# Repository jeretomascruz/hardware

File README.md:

# Hardware Monorepo (KiCad)

Este repositorio agrupa múltiples proyectos de hardware.

## Proyectos
- sensado-soldadoras/: Módulo de sensado (KiCad), con kicad/, outputs/, mechanical/, docs/.

## Flujos
- Versionar releases por proyecto usando tags por convención, por ejemplo: sensado-soldadoras-hw-v1.0 o hw-v1.0 si el repo contiene un único proyecto activo.
- Subir Gerbers/BOM/PickPlace y PDFs a cada Release.
- Usar Git LFS (configurado en .gitattributes) para binarios.

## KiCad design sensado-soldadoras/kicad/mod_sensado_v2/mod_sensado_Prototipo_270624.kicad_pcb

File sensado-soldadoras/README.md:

# Sensado Soldadoras - Hardware (KiCad)

Repositorio de diseños de hardware (KiCad) para el sistema de sensado.

## Estructura
- kicad/: archivos fuente del proyecto KiCad (.kicad_pro, .kicad_sch, .kicad_pcb, librerías)
- outputs/: archivos de fabricación
  - gerbers/, om/, pickplace/, pdf/
- mechanical/: modelos 3D y mecánica (STEP, STL, etc.)
- docs/: documentación, datasheets, fotos

## Buenas prácticas
- Versionado de HW por tags: hw-v1.0, hw-v1.1.
- Adjuntar Gerbers, BOM y Pick&Place en cada Release.
- Usar Git LFS para binarios pesados (STEP/PDF/ZIP).

## Generar outputs
- Exporta Gerbers, BOM (CSV) y Pick&Place desde KiCad y colócalos en outputs/.
- Exporta esquemáticos y PCB a PDF a outputs/pdf/.

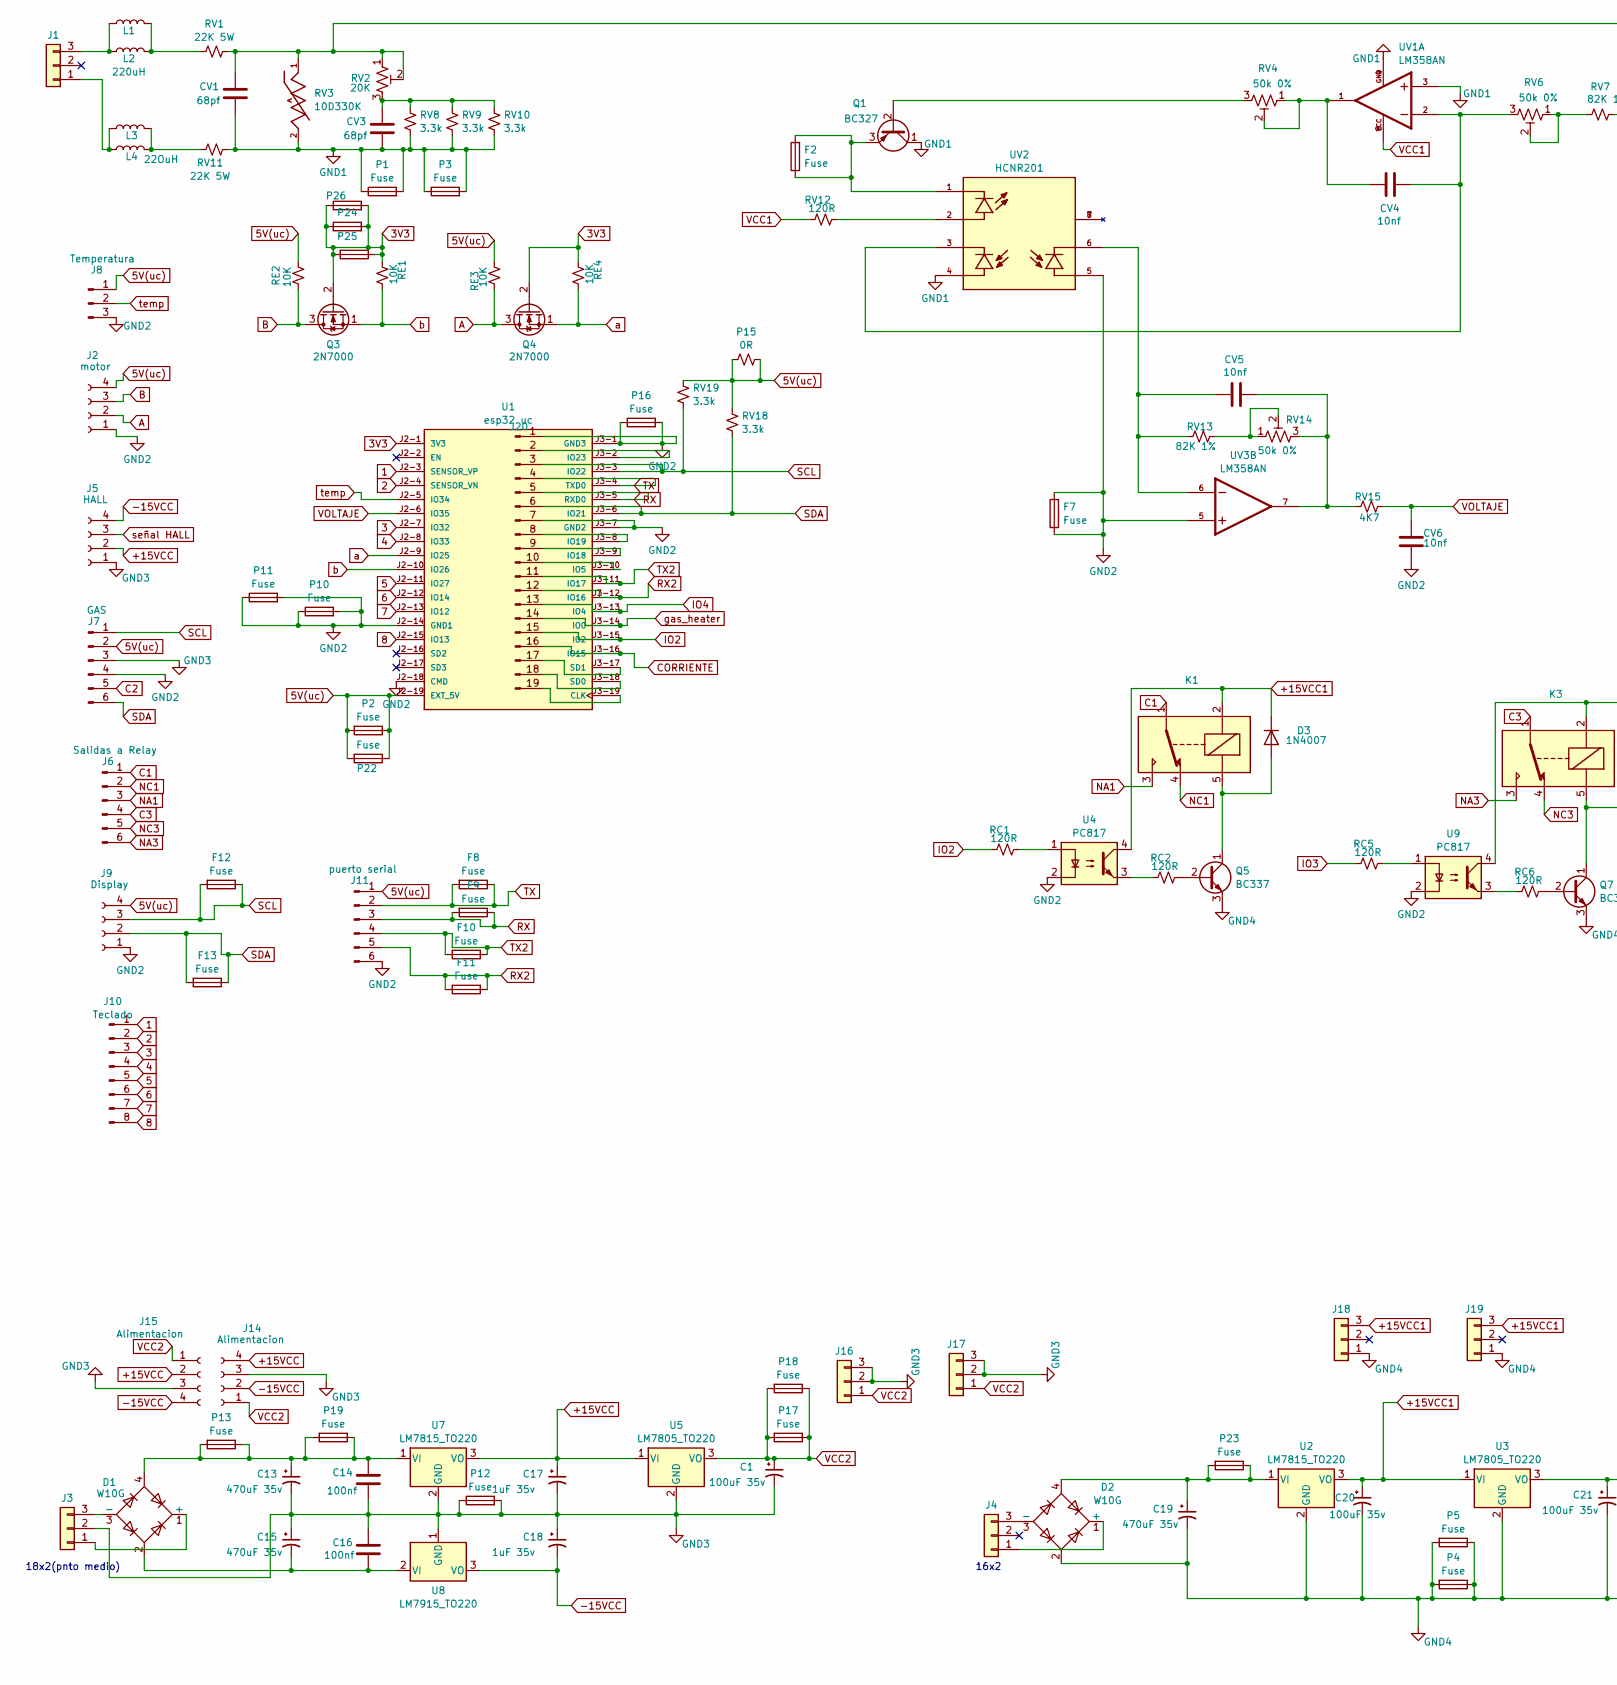
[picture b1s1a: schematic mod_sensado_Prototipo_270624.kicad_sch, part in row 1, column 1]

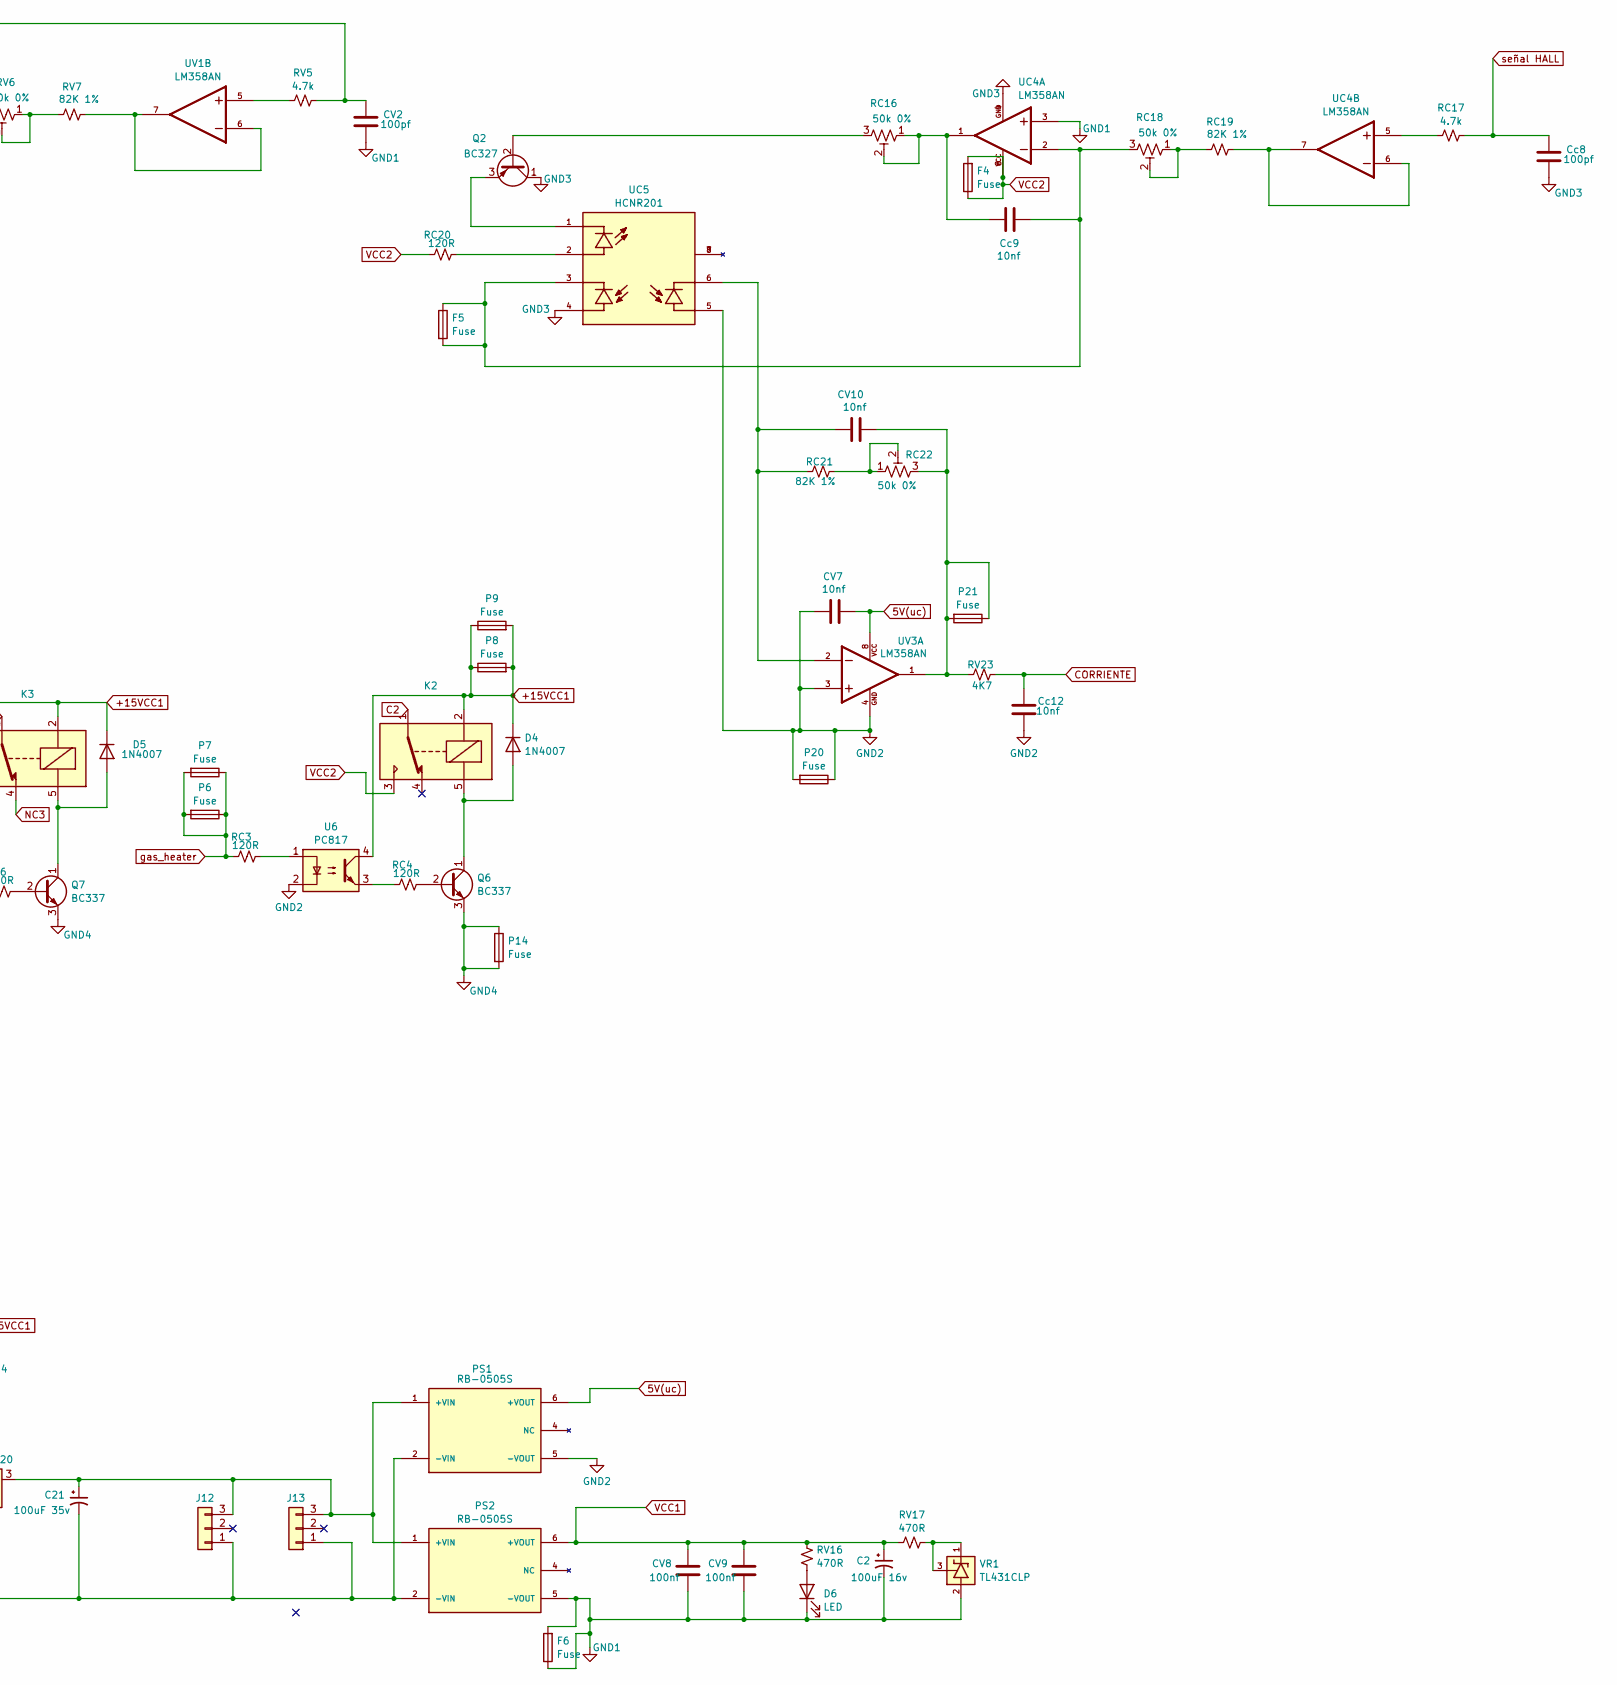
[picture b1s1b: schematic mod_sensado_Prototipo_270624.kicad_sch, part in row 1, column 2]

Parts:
C1, C20, C21: 100uF 35v; CP_Radial_D8.0mm_P2.50mm
C2: 100uF 16v; CP_Radial_D8.0mm_P2.50mm
C13, C15, C19: 470uF 35v; CP_Radial_D8.0mm_P2.50mm
C14, C16: 100nf; C_Disc_D4.7mm_W2.5mm_P5.00mm
C17, C18: 1uF 35v; CP_Radial_D8.0mm_P2.50mm
CV1, CV3: 68pf; C_Disc_D4.7mm_W2.5mm_P5.00mm
CV2: 100pf; C_Disc_D4.7mm_W2.5mm_P5.00mm
CV4, CV5, CV6, CV7, CV10: 10nf; C_Disc_D4.7mm_W2.5mm_P5.00mm
CV8, CV9: 100nf; C_Disc_D4.7mm_W2.5mm_P5.00mm
Cc8: 100pf; C_Disc_D4.7mm_W2.5mm_P5.00mm
Cc9, Cc12: 10nf; C_Disc_D4.7mm_W2.5mm_P5.00mm
D1, D2: W10G; Diode_Bridge_Round_D9.8mm
D3, D4, D5: 1N4007; D_DO-41_SOD81_P10.16mm_Horizontal
D6: LED; LED_D3.0mm_Clear
F2, F4, F5, F6, F7, F8, F9, F10, F11, F12, F13: Fuse; R_Axial_DIN0207_L6.3mm_D2.5mm_P7.62mm_Horizontal
J1, J3, J4, J12, J13, J16, J17, J18, J19: Conn_01x03; Molex_KK-396_5273-03A_1x03_P3.96mm_Vertical
J2: motor; Altech_AK100_1x04_P5.00mm
J5: HALL; Altech_AK100_1x04_P5.00mm
J6: Salidas a Relay; JST_VH_B6P-VH_1x06_P3.96mm_Vertical
J7: GAS; TerminalBlock_MetzConnect_Type205_RT04506UBLC_1x06_P5.00mm_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
J8: Temperatura; Altech_AK100_1x03_P5.00mm
J9: Display; Altech_AK100_1x04_P5.00mm
J10: Teclado; PinHeader_1x10_P2.54mm_Vertical
J11: puerto serial; TerminalBlock_MetzConnect_Type205_RT04506UBLC_1x06_P5.00mm_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
J14, J15: Alimentacion; Molex_KK-396_A-41791-0004_1x04_P3.96mm_Vertical
J20: Conn_01x19_Pin; PinHeader_1x19_P2.54mm_Vertical
K1, K2, K3: SANYOU_SRD_Form_C; Relay_SPDT_SANYOU_SRD_Series_Form_C
L1: 220uH; L_Neosid_SM-PIC0512H
L2: 220uH; L_Axial_L9.5mm_D4.0mm_P12.70mm_Horizontal_Fastron_SMCC
L3: 22OuH; L_Neosid_SM-PIC0512H
L4: 22OuH; L_Axial_L9.5mm_D4.0mm_P12.70mm_Horizontal_Fastron_SMCC
P1, P2, P3, P4, P5, P6, P7, P8, P9, P10, P11, P12, P13, P14, P16, P17, P18, P19, P20, P21, P22, P23, P24, P25, P26: Fuse; R_Axial_DIN0207_L6.3mm_D2.5mm_P7.62mm_Horizontal
P15: 0R; R_Axial_DIN0309_L9.0mm_D3.2mm_P15.24mm_Horizontal
PS1, PS2: RB-0505S; RB-0505S convertidor; PARTREV 0/2015
Q1, Q2: BC327; TO-92_Wide
Q3, Q4: 2N7000; TO-92_Wide
Q5, Q6, Q7: BC337; TO-92_Wide
RC1, RC2, RC3, RC4, RC5, RC6, RC20: 120R; R_Axial_DIN0309_L9.0mm_D3.2mm_P15.24mm_Horizontal
RC16, RC18, RC22: 50k 0%; Potentiometer_Runtron_RM-063_Horizontal
RC17: 4.7k; R_Axial_DIN0309_L9.0mm_D3.2mm_P15.24mm_Horizontal
RC19, RC21: 82K 1%; R_Axial_DIN0309_L9.0mm_D3.2mm_P15.24mm_Horizontal
RE1, RE2, RE3, RE4: 10K; R_Axial_DIN0309_L9.0mm_D3.2mm_P15.24mm_Horizontal
RV1, RV11: 22K 5W; R_Axial_Power_L25.0mm_W9.0mm_P30.48mm
RV2: 20K; Potentiometer_Runtron_RM-063_Horizontal
RV3: 10D330K; Varistor; PARTREV Jan-18
RV4, RV6, RV14: 50k 0%; Potentiometer_Runtron_RM-063_Horizontal
RV5: 4.7k; R_Axial_DIN0309_L9.0mm_D3.2mm_P15.24mm_Horizontal
RV7, RV13: 82K 1%; R_Axial_DIN0309_L9.0mm_D3.2mm_P15.24mm_Horizontal
RV8, RV9, RV10, RV18, RV19: 3.3k; R_Axial_DIN0309_L9.0mm_D3.2mm_P15.24mm_Horizontal
RV12: 120R; R_Axial_DIN0309_L9.0mm_D3.2mm_P15.24mm_Horizontal
RV15, RV23: 4K7; R_Axial_DIN0309_L9.0mm_D3.2mm_P15.24mm_Horizontal
RV16, RV17: 470R; R_Axial_DIN0309_L9.0mm_D3.2mm_P15.24mm_Horizontal
U1: esp32 uc; ESP32-module; PARTREV V4
U2, U7: LM7815_TO220; TO-220-3_Vertical
U3, U5: LM7805_TO220; TO-220-3_Vertical
U4, U6, U9: PC817; DIP-4_W7.62mm
U8: LM7915_TO220; TO-220-3_Vertical
UC4: LM358AN; lm358
UC5: HCNR201; hcn201; PARTREV July 1, 2014
UV1, UV3: LM358AN; lm358
UV2: HCNR201; hcn201; PARTREV July 1, 2014
VR1: TL431CLP; TO-92; PARTREV R

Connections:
1: J10.1, U1.J2-3 (SENSOR_VP)
2: J10.2, U1.J2-4 (SENSOR_VN)
3: J10.3, U1.J2-7 (IO32)
3V3: P24.1, P24.2, P25.1, P25.2, P26.1, P26.2, Q3.2 (G), Q4.2 (G), RE1.2, RE4.2, U1.J2-1 (3V3)
4: J10.4, U1.J2-8 (IO33)
5: J10.5, U1.J2-11 (IO27)
5V(uc): CV7.2, J2.4, J7.2, J8.1, J9.4, J11.1, P2.1, P2.2, P15.1, P15.2, P22.1, P22.2, PS1.6 (+VOUT), RE2.1, RE3.1, RV18.2, RV19.2, U1.J2-19 (EXT_5V), UV3.8
6: J10.6, U1.J2-12 (IO14)
7: J10.7, U1.J2-13 (IO12)
8: J10.8, U1.J2-15 (IO13)
+15VCC: C17.1, J5.2, J14.4, J15.2, U5.1 (VI), U7.3 (VO)
+15VCC1: C20.1, D3.1 (K), D4.1 (K), D5.1 (K), J18.3, J19.3, K1.2, K2.2, K3.2, P8.1, P8.2, P9.1, P9.2, U2.3 (VO), U3.1 (VI), U4.4, U6.4, U9.4
-15VCC: C18.2, J5.4, J14.2, J15.4, U8.3 (VO)
A: J2.2, Q4.3 (D), RE3.2
B: J2.3, Q3.3 (D), RE2.2
C1: J6.1, K1.1
C2: J7.5, K2.1
C3: J6.4, K3.1
CORRIENTE: Cc12.2, J20.16, RV23.2, U1.J3-16 (IO15)
GND1: C2.2, CV1.2, CV2.2, CV3.2, CV8.2, CV9.2, D6.1 (K), F6.1, F6.2, P1.1, P1.2, P3.1, P3.2, PS2.5 (-VOUT), Q1.1 (C), RV3.2, RV8.1, RV9.1, RV10.1, RV11.2, UC4.3, UV1.3, UV1.4, UV2.4, VR1.2
GND2: CV6.1, CV7.1, Cc12.1, F7.1, F7.2, J2.1, J7.4, J8.3, J9.1, J11.6, J20.1, J20.7, P10.1, P10.2, P11.1, P11.2, P16.1, P16.2, P20.1, P20.2, PS1.5 (-VOUT), U1.J2-14 (GND1), U1.J2-18 (CMD), U1.J3-1 (GND3), U1.J3-7 (GND2), U4.2, U6.2, U9.2, UC5.5, UV2.5, UV3.3, UV3.4, UV3.5
GND3: C1.2, C13.2, C14.2, C15.1, C16.1, C17.2, C18.1, Cc8.2, J3.2, J5.1, J7.3, J14.3, J15.3, J16.2, J16.3, J17.2, J17.3, P12.1, P12.2, Q2.1 (C), U5.2 (GND), U7.2 (GND), U8.1 (GND), UC4.4, UC5.4
GND4: C19.2, C20.2, C21.2, D2.2, J12.1, J13.1, J18.1, J19.1, P4.1, P4.2, P5.1, P5.2, P14.1, P14.2, PS1.2 (-VIN), PS2.2 (-VIN), Q5.3 (E), Q6.3 (E), Q7.3 (E), U2.2 (GND), U3.2 (GND)
IO2: J20.15, RC1.2, U1.J3-15 (IO2)
IO3: RC5.2
IO4: J20.13, U1.J3-13 (IO4)
NA1: J6.3, K1.3
NA3: J6.6, K3.3
NC1: J6.2, K1.4
NC3: J6.5, K3.4
unnamed: CV1.1, CV2.1, RV1.2, RV2.1, RV2.2, RV3.1, RV5.1
unnamed: CV3.1, RV2.3, RV8.2, RV9.2, RV10.2
unnamed: CV4.1, RV4.1, RV4.2, UV1.1
unnamed: CV4.2, RV6.3, UV1.2, UV2.3
unnamed: CV5.1, RV13.1, UV2.6, UV3.6
unnamed: CV5.2, RV14.3, RV15.1, UV3.7
unnamed: CV10.1, RC21.1, UC5.6, UV3.2
unnamed: CV10.2, P21.1, P21.2, RC22.3, RV23.1, UV3.1
unnamed: Cc9.1, RC16.1, RC16.2, UC4.1
unnamed: Cc9.2, F5.1, F5.2, RC18.3, UC4.2, UC5.3
unnamed: D1.1 (+), J3.1
unnamed: D1.3 (-), J3.3
unnamed: D2.1 (+), J4.1
unnamed: D2.3 (-), J4.3
unnamed: D3.2 (A), K1.5, Q5.1 (C)
unnamed: D4.2 (A), K2.5, Q6.1 (C)
unnamed: D5.2 (A), K3.5, Q7.1 (C)
unnamed: D6.2 (A), RV16.1
unnamed: J1.1, L3.1, L4.1
unnamed: J1.3, L1.1, L2.1
unnamed: C21.1, J12.3, J13.3, PS1.1 (+VIN), PS2.1 (+VIN), U3.3 (VO)
unnamed: J20.2, U1.J3-2 (IO23)
unnamed: J20.8, U1.J3-8 (IO19)
unnamed: J20.9, U1.J3-9 (IO18)
unnamed: J20.10, U1.J3-10 (IO5)
unnamed: J20.17, U1.J3-17 (SD1)
unnamed: J20.18, U1.J3-18 (SD0)
unnamed: J20.19, U1.J3-19 (CLK)
unnamed: L1.2, L2.2, RV1.1
unnamed: L3.2, L4.2, RV11.1
unnamed: Q1.2 (B), RV4.3
unnamed: F2.1, F2.2, Q1.3 (E), UV2.1
unnamed: Q2.2 (B), RC16.3
unnamed: Q2.3 (E), UC5.1
unnamed: Q5.2 (B), RC2.1
unnamed: Q6.2 (B), RC4.1
unnamed: Q7.2 (B), RC6.1
unnamed: RC1.1, U4.1
unnamed: RC2.2, U4.3
unnamed: RC3.1, U6.1
unnamed: RC4.2, U6.3
unnamed: RC5.1, U9.1
unnamed: RC6.2, U9.3
unnamed: RC17.2, UC4.5
unnamed: RC18.1, RC18.2, RC19.2
unnamed: RC19.1, UC4.6, UC4.7
unnamed: RC20.1, UC5.2
unnamed: RC21.2, RC22.1, RC22.2
unnamed: RV5.2, UV1.5
unnamed: RV6.1, RV6.2, RV7.2
unnamed: RV7.1, UV1.6, UV1.7
unnamed: RV12.1, UV2.2
unnamed: RV13.2, RV14.1, RV14.2
unnamed: RV17.1, VR1.1, VR1.3
unnamed: C19.1, D2.4, P23.1, P23.2, U2.1 (VI)
unnamed: C13.1, C14.1, D1.4, P13.1, P13.2, P19.1, P19.2, U7.1 (VI)
unnamed: C15.2, C16.2, D1.2, U8.2 (VI)
RX: F9.1, F9.2, J11.3, J20.5, U1.J3-5 (RXD0)
RX2: F11.1, F11.2, J11.5, J20.12, U1.J3-12 (IO16)
SCL: F12.1, F12.2, J7.1, J9.3, J20.3, RV19.1, U1.J3-3 (IO22)
SDA: F13.1, F13.2, J7.6, J9.2, J20.6, RV18.1, U1.J3-6 (IO21)
TX: F8.1, F8.2, J11.2, J20.4, U1.J3-4 (TXD0)
TX2: F10.1, F10.2, J11.4, J20.11, U1.J3-11 (IO17)
VCC1: C2.1, CV8.1, CV9.1, PS2.6 (+VOUT), RV12.2, RV16.2, RV17.2, UV1.8
VCC2: C1.1, F4.1, F4.2, J14.1, J15.1, J16.1, J17.1, K2.3, P17.1, P17.2, P18.1, P18.2, RC20.2, U5.3 (VO), UC4.8
VOLTAJE: CV6.2, RV15.2, U1.J2-6 (IO35)
a: Q4.1 (S), RE4.1, U1.J2-9 (IO25)
b: Q3.1 (S), RE1.1, U1.J2-10 (IO26)
gas_heater: J20.14, P6.1, P6.2, P7.1, P7.2, RC3.2, U1.J3-14 (IO0)
señal HALL: Cc8.1, J5.3, RC17.1
temp: J8.2, U1.J2-5 (IO34)

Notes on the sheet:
16x2
18x2(pnto medio)

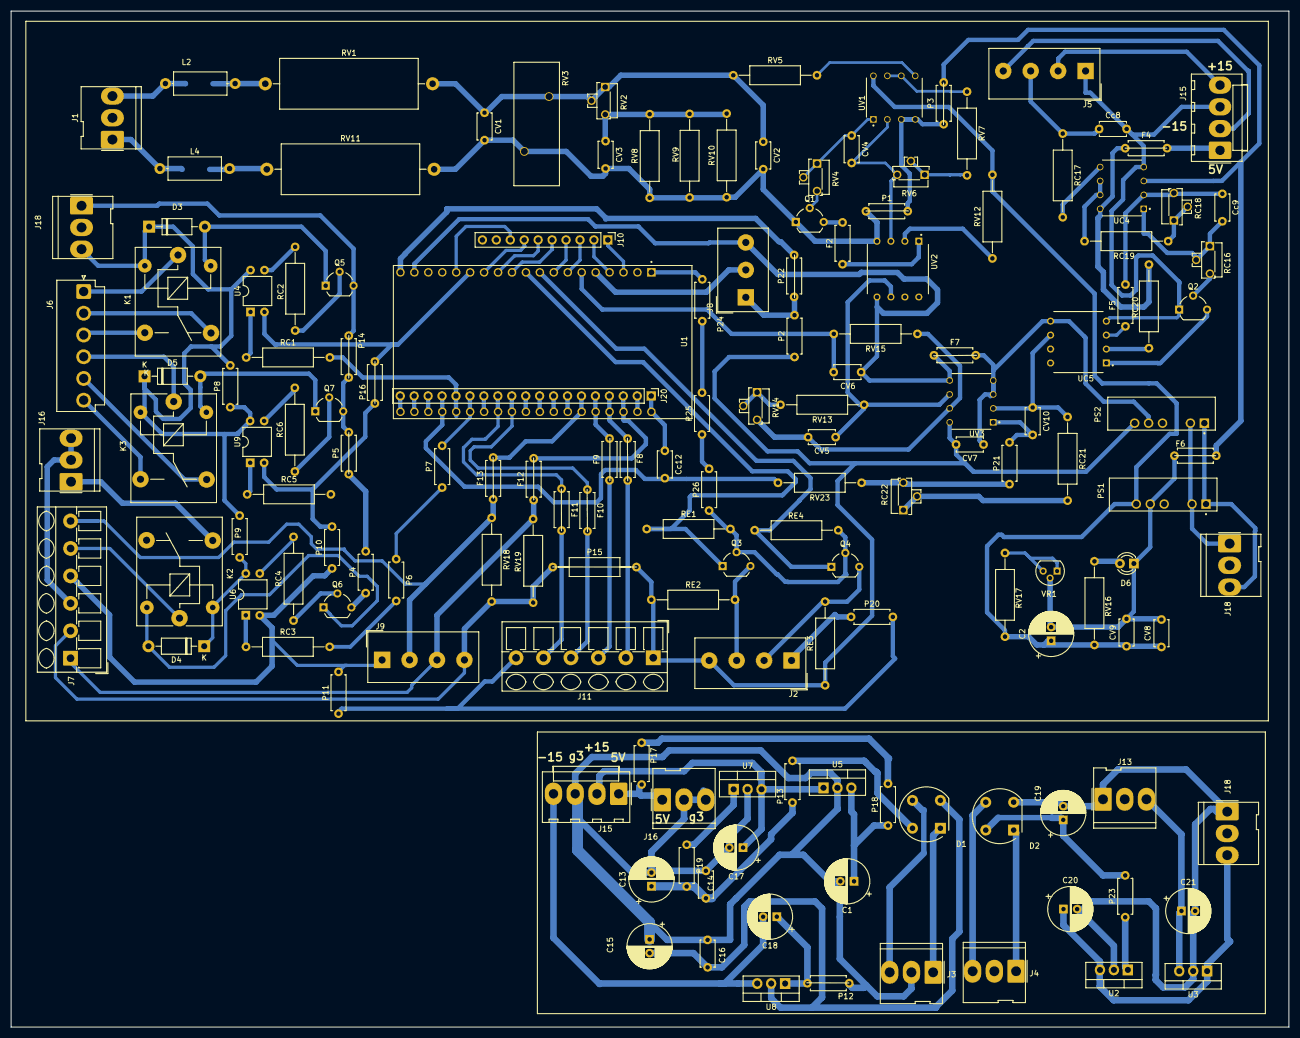
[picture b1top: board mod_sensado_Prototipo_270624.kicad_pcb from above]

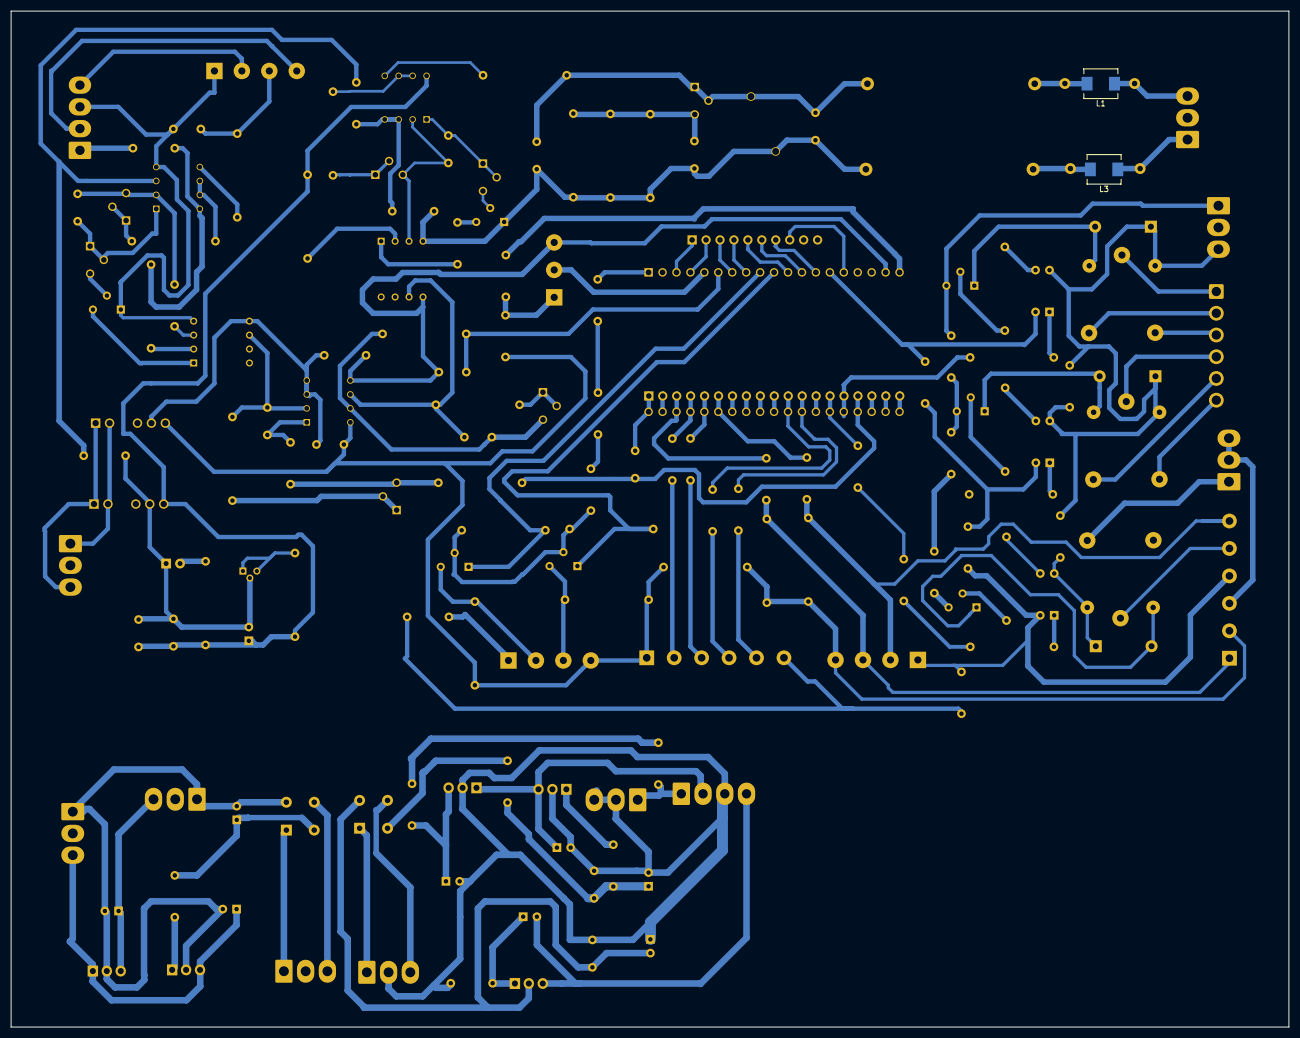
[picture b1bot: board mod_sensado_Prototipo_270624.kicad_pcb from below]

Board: 2 copper layers, 232.8 x 185.1 mm, 155 parts (2 on the bottom side), 100 nets.

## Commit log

2025-10-31 Initial KiCad hardware repo scaffold: structure, .gitignore, LFS, README, CI
2025-10-31 Chore: restructure as monorepo (sensado-soldadoras subdir), update ignores and root README
2025-10-31 Add KiCad project: sensado-soldadoras/mod_sensado_Prototipo_270624
2025-10-31 Start HW v2: duplicate KiCad project into mod_sensado_v2
2025-10-31 Chore: ignore fabrication outputs; remove tracked Gerbers/DXF/PDF
2025-10-31 CI: release workflow accepts project-specific tags (sensado-soldadoras-hw-v*)
